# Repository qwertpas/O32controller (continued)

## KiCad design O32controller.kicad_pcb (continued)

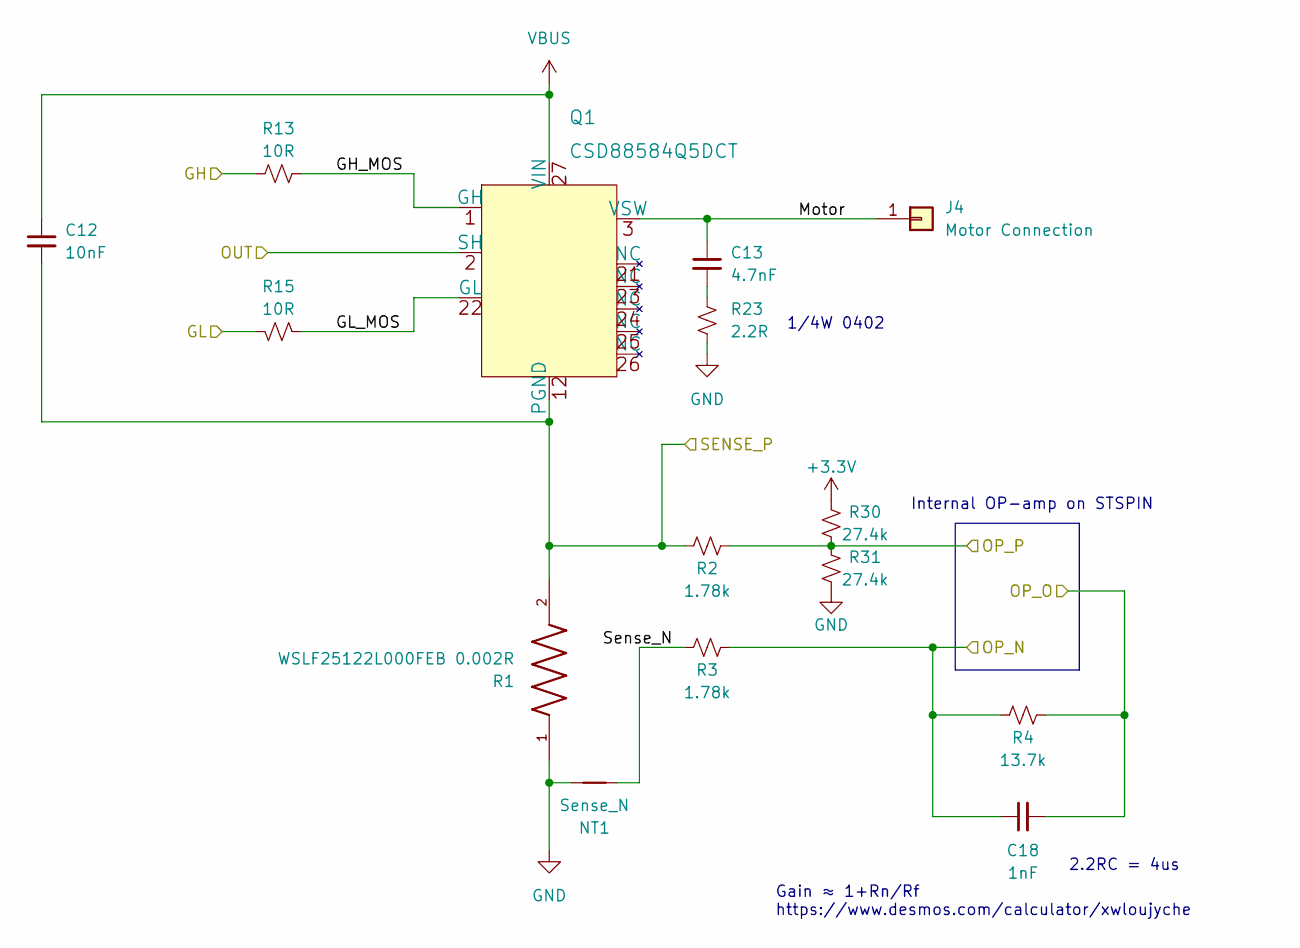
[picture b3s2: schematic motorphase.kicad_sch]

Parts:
C12: 10nF; C_0402_1005Metric
C13: 4.7nF; C_0402_1005Metric
C18: 1nF; C_0402_1005Metric
J4: Motor Connection; SolderWire-Actual_1x01_D1.7mm_OD_2.75mm
NT1: Sense_N; NetTie-2_SMD_Pad0.25mm
Q1: CSD88584Q5DCT
R1: WSLF25122L000FEB 0.002R; R_Shunt_2512_6332Metric
R2, R3: 1.78k; R_0402_1005Metric
R4: 13.7k; R_0402_1005Metric
R13, R15: 10R; R_0402_1005Metric
R23: 2.2R; R_0402_1005Metric
R30, R31: 27.4k; R_0402_1005Metric

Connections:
+3.3V: R30.2; also elsewhere on the board
/HSU: R13.1; also elsewhere on the board
/LSU: R15.2; also elsewhere on the board
/Motor phase U/GH_MOS: Q1.1 (GH), R13.2
/Motor phase U/GL_MOS: Q1.22 (GL), R15.1
/Motor phase U/Motor: C13.1, J4.1, Q1.3 (VSW)
/Motor phase U/SENSE_P: C12.2, Q1.12 (PGND), R1.2, R2.1; also elsewhere on the board
/Motor phase U/Sense_N: NT1.1, R3.1
/OP_U_N: C18.1, R3.2, R4.1; also elsewhere on the board
/OP_U_O: C18.2, R4.2; also elsewhere on the board
/OP_U_P: R2.2, R30.1, R31.2; also elsewhere on the board
/OUTU: Q1.2 (SH); also elsewhere on the board
GND: NT1.2, R1.1, R23.2, R31.1; also elsewhere on the board
unnamed: C13.2, R23.1
VBUS: C12.1, Q1.27 (VIN); also elsewhere on the board

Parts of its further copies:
C14, C16: 10nF; C_0402_1005Metric
C15, C17: 4.7nF; C_0402_1005Metric
C19, C20: 1nF; C_0402_1005Metric
J5, J6: Motor Connection; SolderWire-Actual_1x01_D1.7mm_OD_2.75mm
NT2, NT3: Sense_N; NetTie-2_SMD_Pad0.25mm
Q2, Q3: CSD88584Q5DCT
R5, R9: WSLF25122L000FEB 0.002R; R_Shunt_2512_6332Metric
R6, R7, R10, R11: 1.78k; R_0402_1005Metric
R8, R12: 13.7k; R_0402_1005Metric
R16, R18, R19, R21: 10R; R_0402_1005Metric
R24, R25: 2.2R; R_0402_1005Metric
R32, R33, R34, R35: 27.4k; R_0402_1005Metric

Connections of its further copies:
+3.3V: R32.2, R34.2; also elsewhere on the board
/HSV: R16.1; also elsewhere on the board
/HSW: R19.1; also elsewhere on the board
/LSV: R18.2; also elsewhere on the board
/LSW: R21.2; also elsewhere on the board
/Motor phase V/GH_MOS: Q2.1 (GH), R16.2
/Motor phase V/GL_MOS: Q2.22 (GL), R18.1
/Motor phase V/Motor: C15.1, J5.1, Q2.3 (VSW)
/Motor phase V/SENSE_P: C14.2, Q2.12 (PGND), R5.2, R6.1; also elsewhere on the board
/Motor phase V/Sense_N: NT2.1, R7.1
/Motor phase W/GH_MOS: Q3.1 (GH), R19.2
/Motor phase W/GL_MOS: Q3.22 (GL), R21.1
/Motor phase W/Motor: C17.1, J6.1, Q3.3 (VSW)
/Motor phase W/SENSE_P: C16.2, Q3.12 (PGND), R9.2, R10.1; also elsewhere on the board
/Motor phase W/Sense_N: NT3.1, R11.1
/OP_V_N: C19.1, R7.2, R8.1; also elsewhere on the board
/OP_V_O: C19.2, R8.2; also elsewhere on the board
/OP_V_P: R6.2, R32.1, R33.2; also elsewhere on the board
/OP_W_N: C20.1, R11.2, R12.1; also elsewhere on the board
/OP_W_O: C20.2, R12.2; also elsewhere on the board
/OP_W_P: R10.2, R34.1, R35.2; also elsewhere on the board
/OUTV: Q2.2 (SH); also elsewhere on the board
/OUTW: Q3.2 (SH); also elsewhere on the board
GND: NT2.2, NT3.2, R5.1, R9.1, R24.2, R25.2, R33.1, R35.1; also elsewhere on the board
unnamed: C15.2, R24.1
unnamed: C17.2, R25.1
VBUS: C14.1, C16.1, Q2.27 (VIN), Q3.27 (VIN); also elsewhere on the board

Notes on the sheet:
Internal OP-amp on STSPIN
2.2RC = 4us
Gain ≈ 1+Rn/Rf https://www.desmos.com/calculator/xwloujyche
1/4W 0402

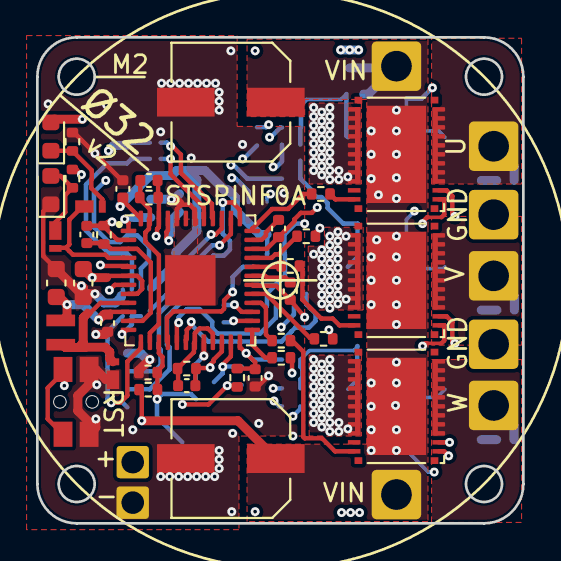
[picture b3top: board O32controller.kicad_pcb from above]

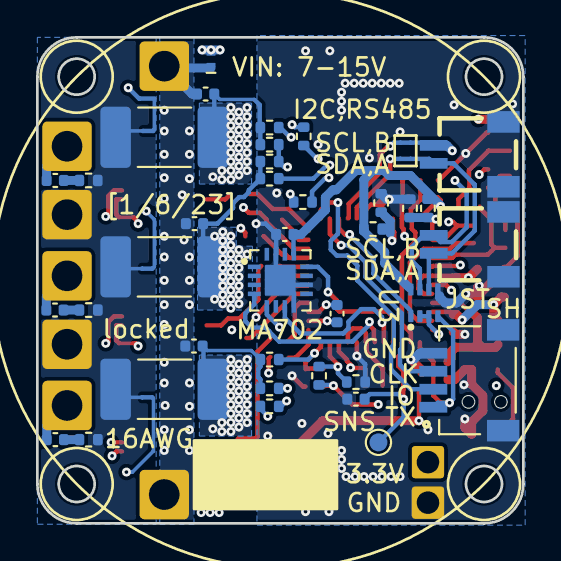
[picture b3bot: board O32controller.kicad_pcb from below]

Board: 4 copper layers, 27.0 x 27.0 mm, 88 parts (42 on the bottom side), 62 nets.

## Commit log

2022-12-17 the beginning :)
2022-12-21 more placement
2022-12-21 put everything on, need to choose caps
2022-12-21 deleted unused Library
2022-12-21 fixed DRC, added as5047D, caps, ind
2022-12-25 before big shunt:
2022-12-25 used 2512 shunts to bridge vias
2022-12-25 ran into problem routing ground trace
2022-12-25 nope I don't think separated motor conns work
2022-12-25 routed some more
2022-12-25 routed some sense, netties, fixed NC
2022-12-26 routed most of power stage, no drc violations
2022-12-26 trying to fix shunt footprint:
2022-12-26 fixed clearances
2022-12-26 routed more signals
2022-12-26 readme
2022-12-27 just need to figure out gpio and buck
2022-12-27 new pic
2022-12-28 i don't like CAN
2022-12-28 assigned gpio and adcs
2023-01-01 added mag702, leds, thought about tx out:
2023-01-03 added rs485 and placed ma702
2023-01-04 ahh my resistor schematic is old:
2023-01-05 woohoo everything connected, no drc err
2023-01-05 choose led, tvs, start on silkscreen
2023-01-05 update pic
2023-01-05 push again
2023-01-06 silkscreen pretty much done
2023-01-06 finish, generate gerbers
2023-01-06 fix mosfet soldermask
2023-01-06 jlcpcb pic
2023-01-09 media
2023-06-11 generate htmlbom
2023-08-23 add front and back pcb view pics
2023-12-24 create new branch v2, prepare for v3
2023-12-26 clean up v2, fix libraries, netties, fix TVS dir
2023-12-26 remove motor conn from ibom, reannotate tvs diode
2023-12-26 restructure into v1,v2,v3 folders
2023-12-26 update readme w v2 pic
2023-12-27 external spi, update bus sns res, routing
2023-12-27 bus caps, finished routing?
2023-12-28 add stitching vias, 0 drc errors
2023-12-28 three versions pic, readme update
2023-12-28 fix readme pic:
2023-12-28 fix readme pic again
2023-12-28 import pcbway cheapest capability drc rules
2023-12-28 increase vias to 0.25 hole 0.55 dia
2023-12-29 export for PCBway
2023-12-30 o12encoder has spi and rs485 option w mcu
2023-12-30 forgot to add o12 directory
2023-12-30 encoder change to both sides FFC
2023-12-30 undo autoroute
2023-12-30 Revert "encoder change to both sides FFC"
    This reverts commit 631d04212b57ce457fbe4c2d518c1d39f3519578.
2023-12-30 actually revert to before autoroute
2023-12-30 use kicad backup 2am
2023-12-30 routed more, trouble with 3.3 and gnd
2023-12-31 done? added silkscreen and pa0 breakout
2023-12-31 clean up schematic
2024-01-03 heatsink step, generate Ø12encoder gerbers:
2024-01-28 update readme pic
2024-03-25 fixed note with OC comparator, 60A 121k error
2024-04-15 Add MIT License
2024-07-29 use MA732 instead of 702, SMF15A
2024-07-30 finalize BOM for v3.1, shared w Axlab
2024-08-10 v3.1 design done, replaced aux spi with uart and 1 gpio, bigger TVS, and MA732
2024-08-10 release v3.1 and generate gerbers
2024-08-10 rename order version and add schematic to readme
